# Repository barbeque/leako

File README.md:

A ColecoVision-compatible games console that you can build yourself!

# License
The Leako project is licensed under [the Creative Commons Attribution-NonCommercial 4.0 license](https://creativecommons.org/licenses/by-nc/4.0/).

# Project Introduction
I originally developed this board in order to play some ColecoVision games that I had gotten from the flea market. This turned into several articles on my old-computer repair blog, Leaded Solder:

 - [Part 1](https://www.leadedsolder.com/2020/02/16/colecovision-diy-part-1.html), covering the impetus and design;
 - [Part 2](https://www.leadedsolder.com/2020/07/10/colecovision-diy-part-2.html), covering the assembly and debugging.
 - [Part 3](https://www.leadedsolder.com/2021/10/14/colecovision-diy-part-3.html), covering "digital" joysticks and the Hand Controller
 - [Part 4](https://www.leadedsolder.com/2021/10/26/colecovision-diy-part-4.html), partially covering "quadrature" joysticks such as the steering wheel and Roller Controller

If you enjoyed this project or if you're interested in contributing to future development, I would greatly appreciate a subscription to [the Leaded Solder Patreon](https://www.patreon.com/leadedsolder). The Patreon not only helps me afford to develop expensive projects like this one, but also includes behind-the-scenes posts and previews of upcoming articles.

# Building It Yourself
First, use a PCB fabrication shop such as JLCPCB or PCBWay to order a Gerber file. You can get those from [the Releases page](https://github.com/barbeque/leako/releases).

Stay tuned for a more involved assembly guide, but early adopters are welcome to assemble and test a board.

For the easiest build, you can install [the Interactive BOM Plugin](https://github.com/openscopeproject/InteractiveHtmlBom) and use KiCad to export it. This will give you a click-through visual BOM that makes it really easy to assemble the board. Future versions of this board will come with one of these files in the Release.

You'll want to consult the BOM PDF for the version of the Leako board you wish to assemble. The first truly "working" version was v0.6. I recommend getting [the Gerber ZIPs and BOM from the Releases page](https://github.com/barbeque/leako/releases).

Not all parts on the BOM (Bill of Materials) can be obtained new. Many components are salvaged and can be obtained from eBay or other Chinese-market surplus stores such as AliExpress. Because the sellers and availability are changing constantly, I unfortunately cannot recommend a specific vendor. I suggest ordering from multiple different sellers and building more Leakos with all the leftover parts :)

For a quicker checkout process, [I have constructed a Digi-Key "list"](https://www.digikey.ca/en/mylists/list/FZA1NMR795) which can help you add all of the "new" parts necessary quickly. 

Namely, you will need to find:
 - A TI TMS9918A/TMS9918ANL (_not_ TMS9118, TMS9119, TMS9929, or TMS9928) VDP;
 - A TI SN76489 sound chip;
 - A 27c512-compatible EPROM (a 27c256 may also work but has not been tested);
 - ColecoVision cartridge games;
 - A ColecoVision-compatible controller

Please note the Leako has, so far, only been constructed and tested in NTSC regions. A PAL version would be a very interesting conversion, but would use a chip like a TMS9919 as well as probably some other board changes.

You will also need a USB power supply and a USB-B cable. I recommend using a USB power supply capable of at least 2A - although I have only measured ~450mA max in practice, it would not be a bad idea to have some additional headroom. A lower-quality supply is also likely to introduce more noise. I have tested with two models of Anker PowerPort.

Please also note that at the time of publication, a silicon and fabrication shortage has meant that many parts (for instance, the TI TPS60403 -5V voltage inverter) have become difficult and/or more expensive to locate than when the machine was originally designed. Some have been substituted, but there are likely others.

## Tools
The ColecoVision games and console rely on the presence of a BIOS ROM. In order to program the EPROM with the BIOS, you'll need a copy of the BIOS (it can be dumped from a real ColecoVision) and an EPROM programmer such as a TL866II+.

For soldering surface-mount parts, I strongly recommend a good temperature-controlled soldering iron such as a Hakko FX-888, paste flux, and quality leaded solder from a brand like Kester or MG Chemical. You can use lead-free solder, but I haven't.

# Compatibility
If you have built your own Leako and tested it with a game that's not listed here, please submit a pull request to add it to this list.

| Game          | Works? | Notes |
|---------------|--------|-------|
| Donkey Kong   | Yes    |       |
| Zaxxon        | Yes    |       |
| Time Pilot    | Yes    |       |
| Carnival      | Yes    |       |
| Frenzy        | Yes    |       |
| Ken Uston's Black Jack / Poker | Yes    |       |
| Looping 	| Yes	 |	 |
| Omega Race	| Yes	 | Tested with Hand Controller |

| Peripheral    | Works? | Notes |
|---------------|--------|-------|
| ColecoVision controller | Yes | |
| ADAM controller | Yes | |
| Super Action Controller | Yes | Tested with _Super Action Baseball_ only |
| Roller Controller | Partial | Tested with _Slither_ only; my controller is not working properly, even on a real ColecoVision |
| Expansion Module #2 (steering controller) | Partial | Tested with _Turbo_ only; my controller is not working properly, even on a real ColecoVision |

The latter two will be re-investigated as the controllers are tested, and hopefully this table will be updated with some better news in the future.

Please note:
 * The Leako board does not have a ColecoVision expansion connector, so it cannot work with any Expansion Modules, including the ADAM.
 * The Leako board does not have a ColecoVision power connector, so the Roller Controller will need to be powered independently using a ColecoVision power supply such as the ColUSB, or wired for a +5V source such as a USB cable.

# Known Issues
## "Always On" phenomenon
If you power the Leako off a monitor or television set that is also being used to display the Leako, it can complete the "ground" circuit from the USB jack through the composite video jack and keep the Leako turned on, bypassing the power switch entirely. In this scenario, the Leako will remain powered on, regardless of the power switch position.

To work around this problem, try powering the Leako from a different USB power source, or use a television that isolates USB ground from video ground.

Thank you to Cheshire Noir and Tom Storey for figuring this one out.

# Version History
## v0.8
More small fixes.
 * Move U20/U11 to other side of board so cartridges with extra long skirts or loose PCBs won't interfere with them.
 * Move mounting hole added in previous step to side of cartridge slot, so you don't have to use a low-profile screw head there anymore.
 * Larger pads on the 74LS574s, to ease soldering.
 * It is now much harder to hit the video filtering capacitor with the tip of a video cable.
 * Upgraded project files to KiCad 6

## v0.7
Many small fixes, mostly around reliability.
 * Correct missing junction from D3/D4 to R35 (EXT_QUAD pulldown.) Thank you to Oliver Fiero for catching this.
 * Unused logic inputs grounded to reduce power consumption.
 * Change controller ports from generic KiCad DE9 footprint to AE10968-ND
 * Change -5V charge pump because of parts shortage. Now ICL7660.
 * Controller port numbers on schematic now reflect actual logical controller ports.
 * Barrel jack 5V replaced with USB-B to broaden availability of high-quality regulated power supplies.
 * Additional mounting hole behind cartridge to reduce amount of board flex when cartridges are inserted and removed.
 * Thicker power traces.
 * Passives now labeled on board where possible, to speed assembly.

## v0.6
First working version.

# Links
 - [Console5 schematics and parts list](https://console5.com/wiki/Colecovision)
 - ChildOfCv's [better schematics](https://atariage.com/forums/topic/285656-new-colecovision-schematics/)
 - [Datasheet for LC331632M-12 SRAM](https://www.datasheet4u.com/datasheet-pdf/Sanyo/LC331632M-12/pdf.php?id=391797)
 - [Leonardo Miliani's SRAM video mod](https://www.leonardomiliani.com/en/2019/lm80c-tms9918a/)

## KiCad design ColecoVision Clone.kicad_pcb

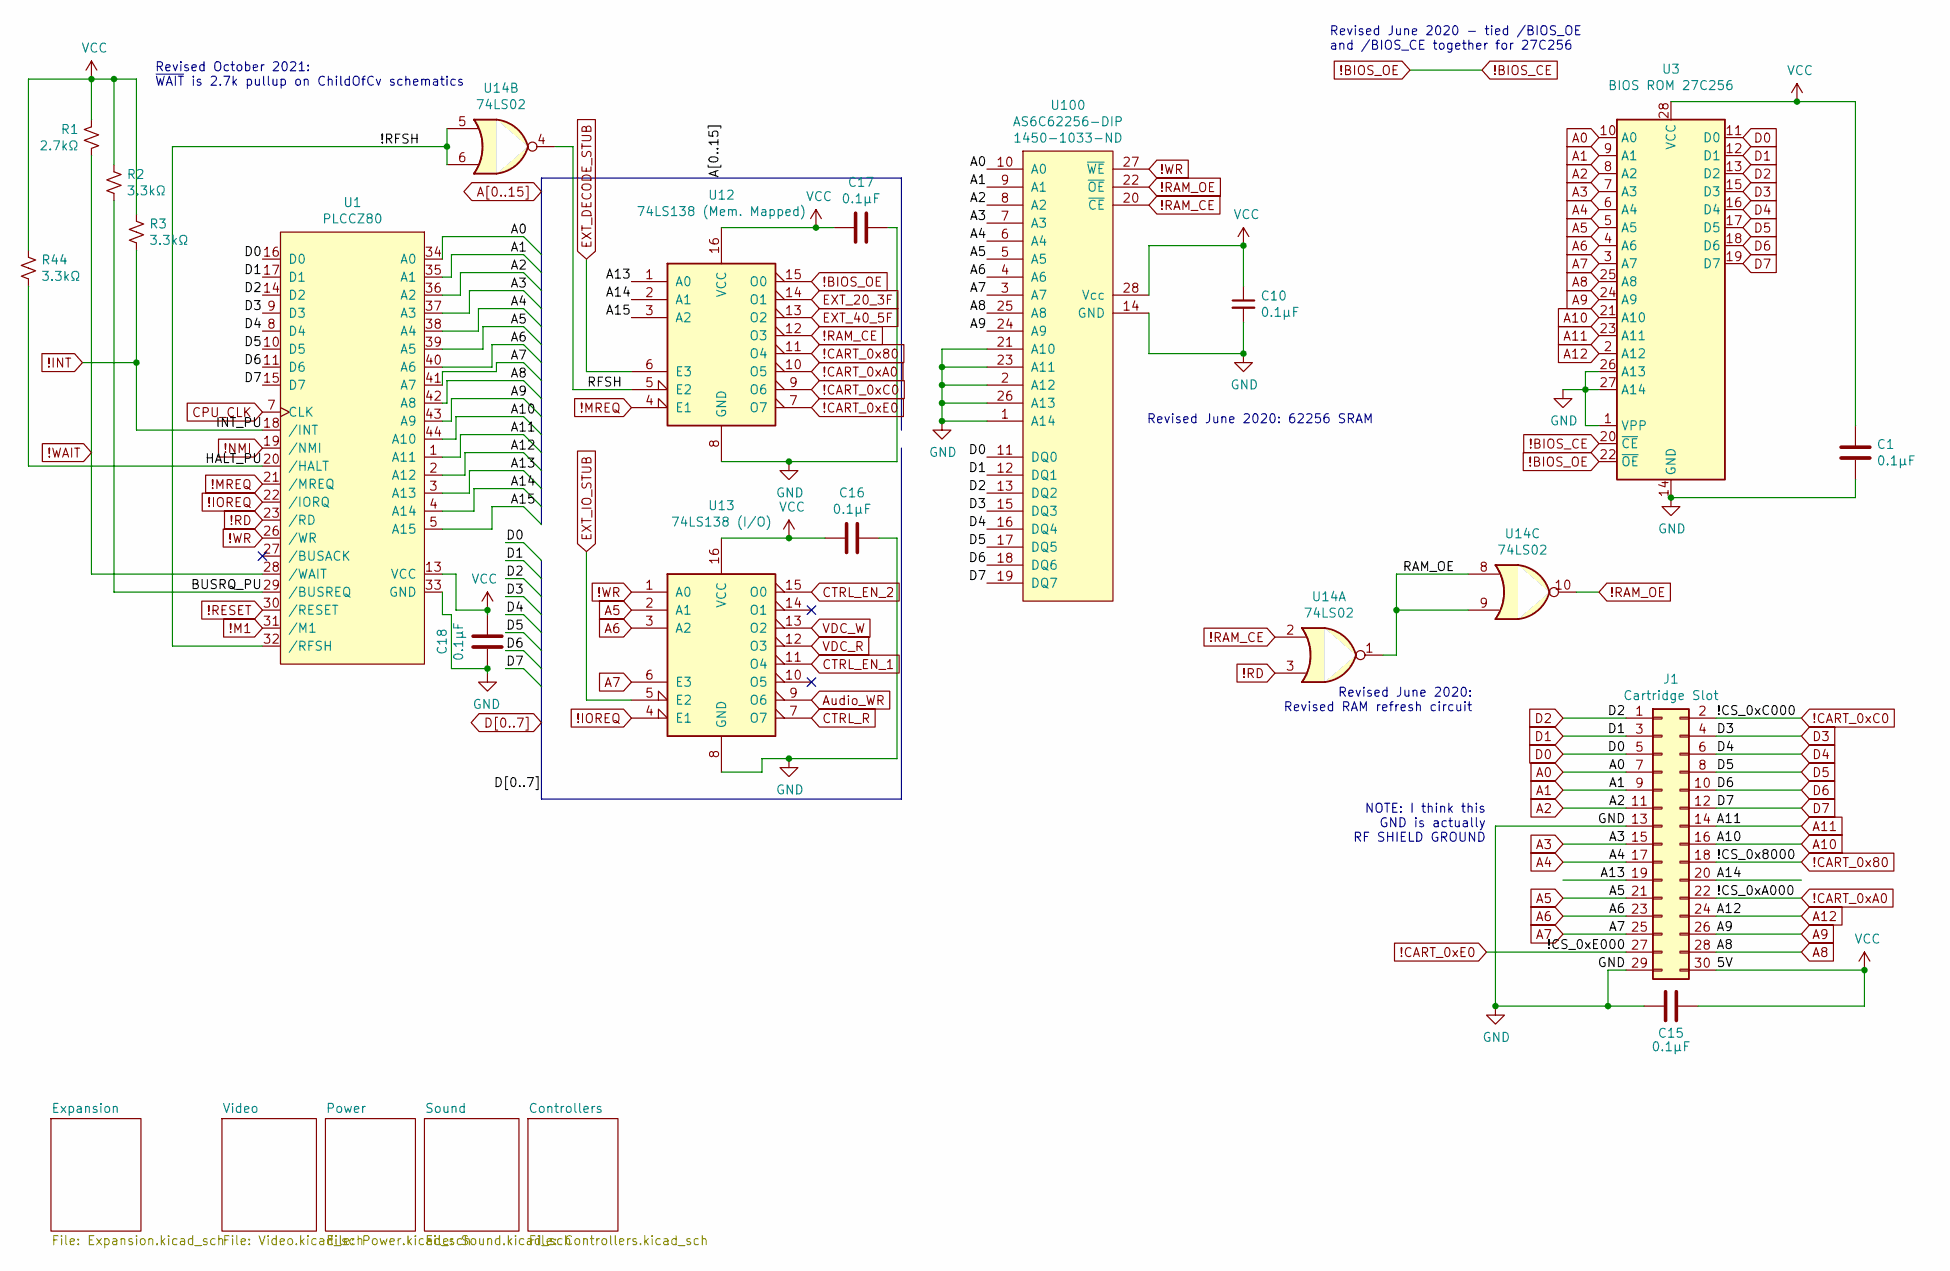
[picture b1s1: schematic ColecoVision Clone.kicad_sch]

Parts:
C1, C10, C15, C16, C17, C18: 0.1µF; C_0805_HandSoldering; DigiKey 1276-1099-1-ND
J1: Cartridge Slot; Sullins_Cart_Slot; DigiKey A31715-ND
R1: 2.7kΩ; R_0805_HandSoldering; DigiKey RMCF0805JT2K70CT-ND
R2, R3, R44: 3.3kΩ; R_0805_HandSoldering; DigiKey RMCF0805JT3K30CT-ND
U1: PLCCZ80; PLCC44; DigiKey 2057-PLCC-44-AT-ND; 269-3899-ND
U3: BIOS ROM 27C256; DIP-28_W15.24mm_Socket_LongPads; DigiKey 2057-ICS-628-T-ND
U12: 74LS138 (Mem. Mapped); SOIC-16_3.9x9.9mm_Pitch1.27mm; DigiKey 296-14883-2-ND
U13: 74LS138 (I/O); SOIC-16_3.9x9.9mm_Pitch1.27mm; DigiKey 296-14883-2-ND
U14: 74LS02; SOIC-14_3.9x8.7mm_Pitch1.27mm; DigiKey 296-14874-1-ND
U100: AS6C62256-DIP; DIP-28_W15.24mm_Socket_LongPads; DigiKey 1450-1033-ND

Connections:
!BIOS_CE: U3.20 (~CE), U3.22 (~OE), U12.15 (O0)
!CART_0x80: J1.18, U12.11 (O4)
!CART_0xA0: J1.22, U12.10 (O5)
!CART_0xC0: J1.2, U12.9 (O6)
!CART_0xE0: J1.27, U12.7 (O7)
!INT: R3.2, U1.18 (/INT); also elsewhere on the board
!IOREQ: U1.22 (/IORQ), U13.4 (E1)
!M1: U1.31 (/M1); also elsewhere on the board
!MREQ: U1.21 (/MREQ), U12.4 (E1)
!NMI: U1.19 (/NMI); also elsewhere on the board
!RAM_CE: U12.12 (O3), U14.2, U100.20 (~CE)
!RAM_OE: U14.10, U100.22 (~OE)
!RD: U1.23 (/RD), U14.3
!RESET: U1.30 (/RESET); also elsewhere on the board
!WAIT: R1.2, U1.28 (/WAIT); also elsewhere on the board
!WR: U1.26 (/WR), U13.1 (A0), U100.27 (~WE)
/!RFSH: U1.32 (/RFSH), U14.5, U14.6
/BUSRQ_PU: R2.2, U1.29 (/BUSREQ)
/HALT_PU: R44.2, U1.20 (/HALT)
/RAM_OE: U14.1, U14.8, U14.9
/RFSH: U12.5 (E2), U14.4
A0: J1.7, U1.34 (A0), U3.10 (A0), U100.10 (A0); also elsewhere on the board
A1: J1.9, U1.35 (A1), U3.9 (A1), U100.9 (A1); also elsewhere on the board
A2: J1.11, U1.36 (A2), U3.8 (A2), U100.8 (A2)
A3: J1.15, U1.37 (A3), U3.7 (A3), U100.7 (A3)
A4: J1.17, U1.38 (A4), U3.6 (A4), U100.6 (A4)
A5: J1.21, U1.39 (A5), U3.5 (A5), U13.2 (A1), U100.5 (A5)
A6: J1.23, U1.40 (A6), U3.4 (A6), U13.3 (A2), U100.4 (A6)
A7: J1.25, U1.41 (A7), U3.3 (A7), U13.6 (E3), U100.3 (A7)
A8: J1.28, U1.42 (A8), U3.25 (A8), U100.25 (A8)
A9: J1.26, U1.43 (A9), U3.24 (A9), U100.24 (A9)
A10: J1.16, U1.44 (A10), U3.21 (A10)
A11: J1.14, U1.1 (A11), U3.23 (A11)
A12: J1.24, U1.2 (A12), U3.2 (A12)
A13: J1.19, U1.3 (A13), U12.1 (A0)
A14: J1.20, U1.4 (A14), U12.2 (A1)
A15: U1.5 (A15), U12.3 (A2)
Audio_WR: U13.9 (O6); also elsewhere on the board
CPU_CLK: U1.7 (CLK); also elsewhere on the board
CTRL_EN_1: U13.11 (O4); also elsewhere on the board
CTRL_EN_2: U13.15 (O0); also elsewhere on the board
CTRL_R: U13.7 (O7); also elsewhere on the board
D0: J1.5, U1.16 (D0), U3.11 (D0), U100.11 (DQ0); also elsewhere on the board
D1: J1.3, U1.17 (D1), U3.12 (D1), U100.12 (DQ1); also elsewhere on the board
D2: J1.1, U1.14 (D2), U3.13 (D2), U100.13 (DQ2); also elsewhere on the board
D3: J1.4, U1.9 (D3), U3.15 (D3), U100.15 (DQ3); also elsewhere on the board
D4: J1.6, U1.8 (D4), U3.16 (D4), U100.16 (DQ4); also elsewhere on the board
D5: J1.8, U1.10 (D5), U3.17 (D5), U100.17 (DQ5); also elsewhere on the board
D6: J1.10, U1.11 (D6), U3.18 (D6), U100.18 (DQ6); also elsewhere on the board
D7: J1.12, U1.15 (D7), U3.19 (D7), U100.19 (DQ7); also elsewhere on the board
EXT_20_3F: U12.14 (O1)
EXT_40_5F: U12.13 (O2)
EXT_DECODE_STUB: U12.6 (E3); also elsewhere on the board
EXT_IO_STUB: U13.5 (E2); also elsewhere on the board
GND: C1.2, C10.2, C15.2, C16.1, C17.2, C18.1, J1.13, J1.29, U1.33 (GND), U3.1 (VPP), U3.14 (GND), U3.26 (A13), U3.27 (A14), U12.8 (GND), U13.8 (GND), U100.1 (A14), U100.2 (A12), U100.14 (GND), U100.21 (A10), U100.23 (A11), U100.26 (A13); also elsewhere on the board
VCC: C1.1, C10.1, C15.1, C16.2, C17.1, C18.2, J1.30, R1.1, R2.1, R3.1, R44.1, U1.13 (VCC), U3.28 (VCC), U12.16 (VCC), U13.16 (VCC), U100.28 (Vcc); also elsewhere on the board
VDC_R: U13.12 (O3); also elsewhere on the board
VDC_W: U13.13 (O2); also elsewhere on the board

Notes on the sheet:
Revised June 2020: Revised RAM refresh circuit
Revised June 2020: 62256 SRAM
Revised June 2020 - tied /BIOS_OE and /BIOS_CE together for 27C256
Revised October 2021: ~{WAIT} is 2.7k pullup on ChildOfCv schematics
NOTE: I think this GND is actually RF SHIELD GROUND

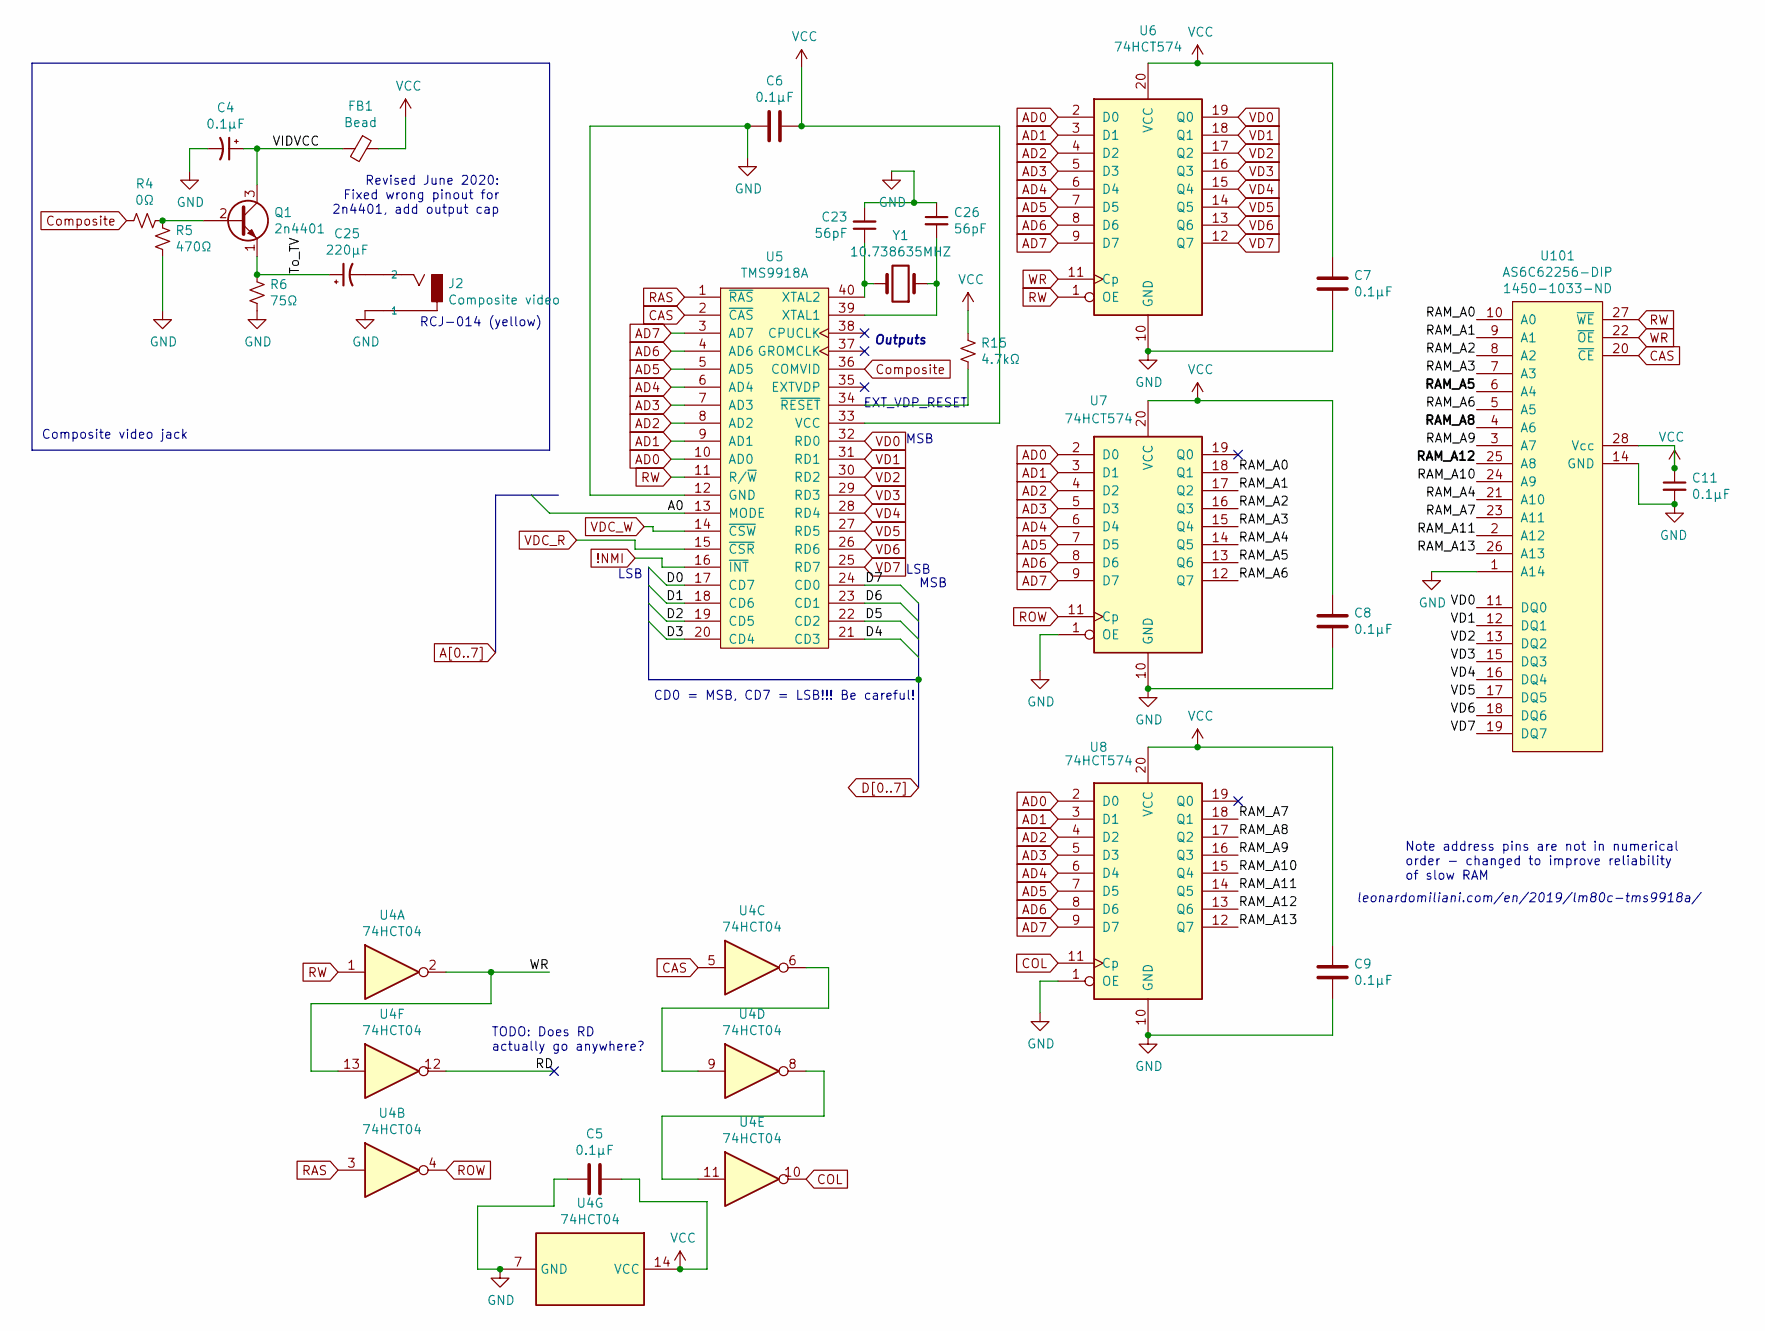
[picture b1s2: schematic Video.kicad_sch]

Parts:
C4, C5, C6, C7, C8, C9, C11: 0.1µF; C_0805_HandSoldering; DigiKey 1276-1099-1-ND
C23, C26: 56pF; C_0805_HandSoldering; DigiKey 732-7817-1-ND
C25: 220µF; CP_Radial_D6.3mm_P2.50mm; DigiKey 493-15121-ND
FB1: Bead; Choke_SMD_1206_Handsoldering; DigiKey 283-MFBW1V3216-310-RCT-ND
J2: Composite video; CUI_RCJ-017; DigiKey CP-1403-ND‎
Q1: 2n4401; TO-92_Inline_Wide; DigiKey 2N4401TFCT-ND
R4: 0Ω; R_0805_HandSoldering; DigiKey RMCF0805ZT0R00CT-ND
R5: 470Ω; R_0805_HandSoldering; DigiKey RMCF0805JT470RCT-ND
R6: 75Ω; R_0805_HandSoldering; DigiKey RMCF0805JT75R0CT-ND
R15: 4.7kΩ; R_0805_HandSoldering; DigiKey RMCF0805JT4K70CT-ND
U4: 74HCT04; SOIC-14_3.9x8.7mm_Pitch1.27mm; DigiKey 296-31832-1-ND
U5: TMS9918A; DIP-40_W15.24mm_Socket_LongPads; DigiKey ED3048-5-ND
U6, U7, U8: 74HCT574; SOIC-20W_7.5x12.8mm_P1.27mm_LongLegs; DigiKey 1727-2856-1-ND
U101: AS6C62256-DIP; DIP-28_W15.24mm_Socket_LongPads; DigiKey 1450-1033-ND
Y1: 10.738635MHZ; Crystal_HC49-U_Vertical; DigiKey CTX1443-ND

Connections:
!NMI: U5.16 (~INT); also elsewhere on the board
/Video/RAM_A0: U7.18 (Q1), U101.10 (A0)
/Video/RAM_A1: U7.17 (Q2), U101.9 (A1)
/Video/RAM_A2: U7.16 (Q3), U101.8 (A2)
/Video/RAM_A3: U7.15 (Q4), U101.7 (A3)
/Video/RAM_A4: U7.14 (Q5), U101.21 (A10)
/Video/RAM_A5: U7.13 (Q6), U101.6 (A4)
/Video/RAM_A6: U7.12 (Q7), U101.5 (A5)
/Video/RAM_A7: U8.18 (Q1), U101.23 (A11)
/Video/RAM_A8: U8.17 (Q2), U101.4 (A6)
/Video/RAM_A9: U8.16 (Q3), U101.3 (A7)
/Video/RAM_A10: U8.15 (Q4), U101.24 (A9)
/Video/RAM_A11: U8.14 (Q5), U101.2 (A12)
/Video/RAM_A12: U8.13 (Q6), U101.25 (A8)
/Video/RAM_A13: U8.12 (Q7), U101.26 (A13)
/Video/RD: U4.12
/Video/To_TV: C25.1, Q1.1 (E), R6.1
/Video/VIDVCC: C4.1, FB1.2, Q1.3 (C)
A0: U5.13 (MODE); also elsewhere on the board
AD0: U5.10 (AD0), U6.2 (D0), U7.2 (D0), U8.2 (D0)
AD1: U5.9 (AD1), U6.3 (D1), U7.3 (D1), U8.3 (D1)
AD2: U5.8 (AD2), U6.4 (D2), U7.4 (D2), U8.4 (D2)
AD3: U5.7 (AD3), U6.5 (D3), U7.5 (D3), U8.5 (D3)
AD4: U5.6 (AD4), U6.6 (D4), U7.6 (D4), U8.6 (D4)
AD5: U5.5 (AD5), U6.7 (D5), U7.7 (D5), U8.7 (D5)
AD6: U5.4 (AD6), U6.8 (D6), U7.8 (D6), U8.8 (D6)
AD7: U5.3 (AD7), U6.9 (D7), U7.9 (D7), U8.9 (D7)
CAS: U4.5, U5.2 (~CAS), U101.20 (~CE)
COL: U4.10, U8.11 (Cp)
Composite: R4.2, U5.36 (COMVID)
D0: U5.17 (CD7); also elsewhere on the board
D1: U5.18 (CD6); also elsewhere on the board
D2: U5.19 (CD5); also elsewhere on the board
D3: U5.20 (CD4); also elsewhere on the board
D4: U5.21 (CD3); also elsewhere on the board
D5: U5.22 (CD2); also elsewhere on the board
D6: U5.23 (CD1); also elsewhere on the board
D7: U5.24 (CD0); also elsewhere on the board
GND: C4.2, C5.2, C6.2, C7.2, C8.2, C9.2, C11.2, C23.2, C26.1, J2.1A (1), J2.1B (1), J2.1C (1), R5.2, R6.2, U4.7 (GND), U5.12 (GND), U6.10 (GND), U7.1 (OE), U7.10 (GND), U8.1 (OE), U8.10 (GND), U101.1 (A14), U101.14 (GND); also elsewhere on the board
unnamed: C23.1, U5.40 (XTAL2), Y1.2
unnamed: C25.2, J2.2
unnamed: C26.2, U5.39 (XTAL1), Y1.1
unnamed: Q1.2 (B), R4.1, R5.1
unnamed: R15.2, U5.34 (~RESET)
unnamed: U4.6, U4.9
unnamed: U4.8, U4.11
RAS: U4.3, U5.1 (~RAS)
ROW: U4.4, U7.11 (Cp)
RW: U4.1, U5.11 (R/~W), U6.1 (OE), U101.27 (~WE)
VCC: C5.1, C6.1, C7.1, C8.1, C9.1, C11.1, FB1.1, R15.1, U4.14 (VCC), U5.33 (VCC), U6.20 (VCC), U7.20 (VCC), U8.20 (VCC), U101.28 (Vcc); also elsewhere on the board
VD0: U5.32 (RD0), U6.19 (Q0), U101.11 (DQ0)
VD1: U5.31 (RD1), U6.18 (Q1), U101.12 (DQ1)
VD2: U5.30 (RD2), U6.17 (Q2), U101.13 (DQ2)
VD3: U5.29 (RD3), U6.16 (Q3), U101.15 (DQ3)
VD4: U5.28 (RD4), U6.15 (Q4), U101.16 (DQ4)
VD5: U5.27 (RD5), U6.14 (Q5), U101.17 (DQ5)
VD6: U5.26 (RD6), U6.13 (Q6), U101.18 (DQ6)
VD7: U5.25 (RD7), U6.12 (Q7), U101.19 (DQ7)
VDC_R: U5.15 (~CSR); also elsewhere on the board
VDC_W: U5.14 (~CSW); also elsewhere on the board
WR: U4.2, U4.13, U6.11 (Cp), U101.22 (~OE)

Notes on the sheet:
leonardomiliani.com/en/2019/lm80c-tms9918a/
TODO: Does RD actually go anywhere?
EXT_VDP_RESET
LSB
CD0 = MSB, CD7 = LSB!!! Be careful!
Composite video jack
Note address pins are not in numerical order - changed to improve reliability of slow RAM
RCJ-014 (yellow)
Revised June 2020: Fixed wrong pinout for 2n4401, add output cap
MSB
Outputs

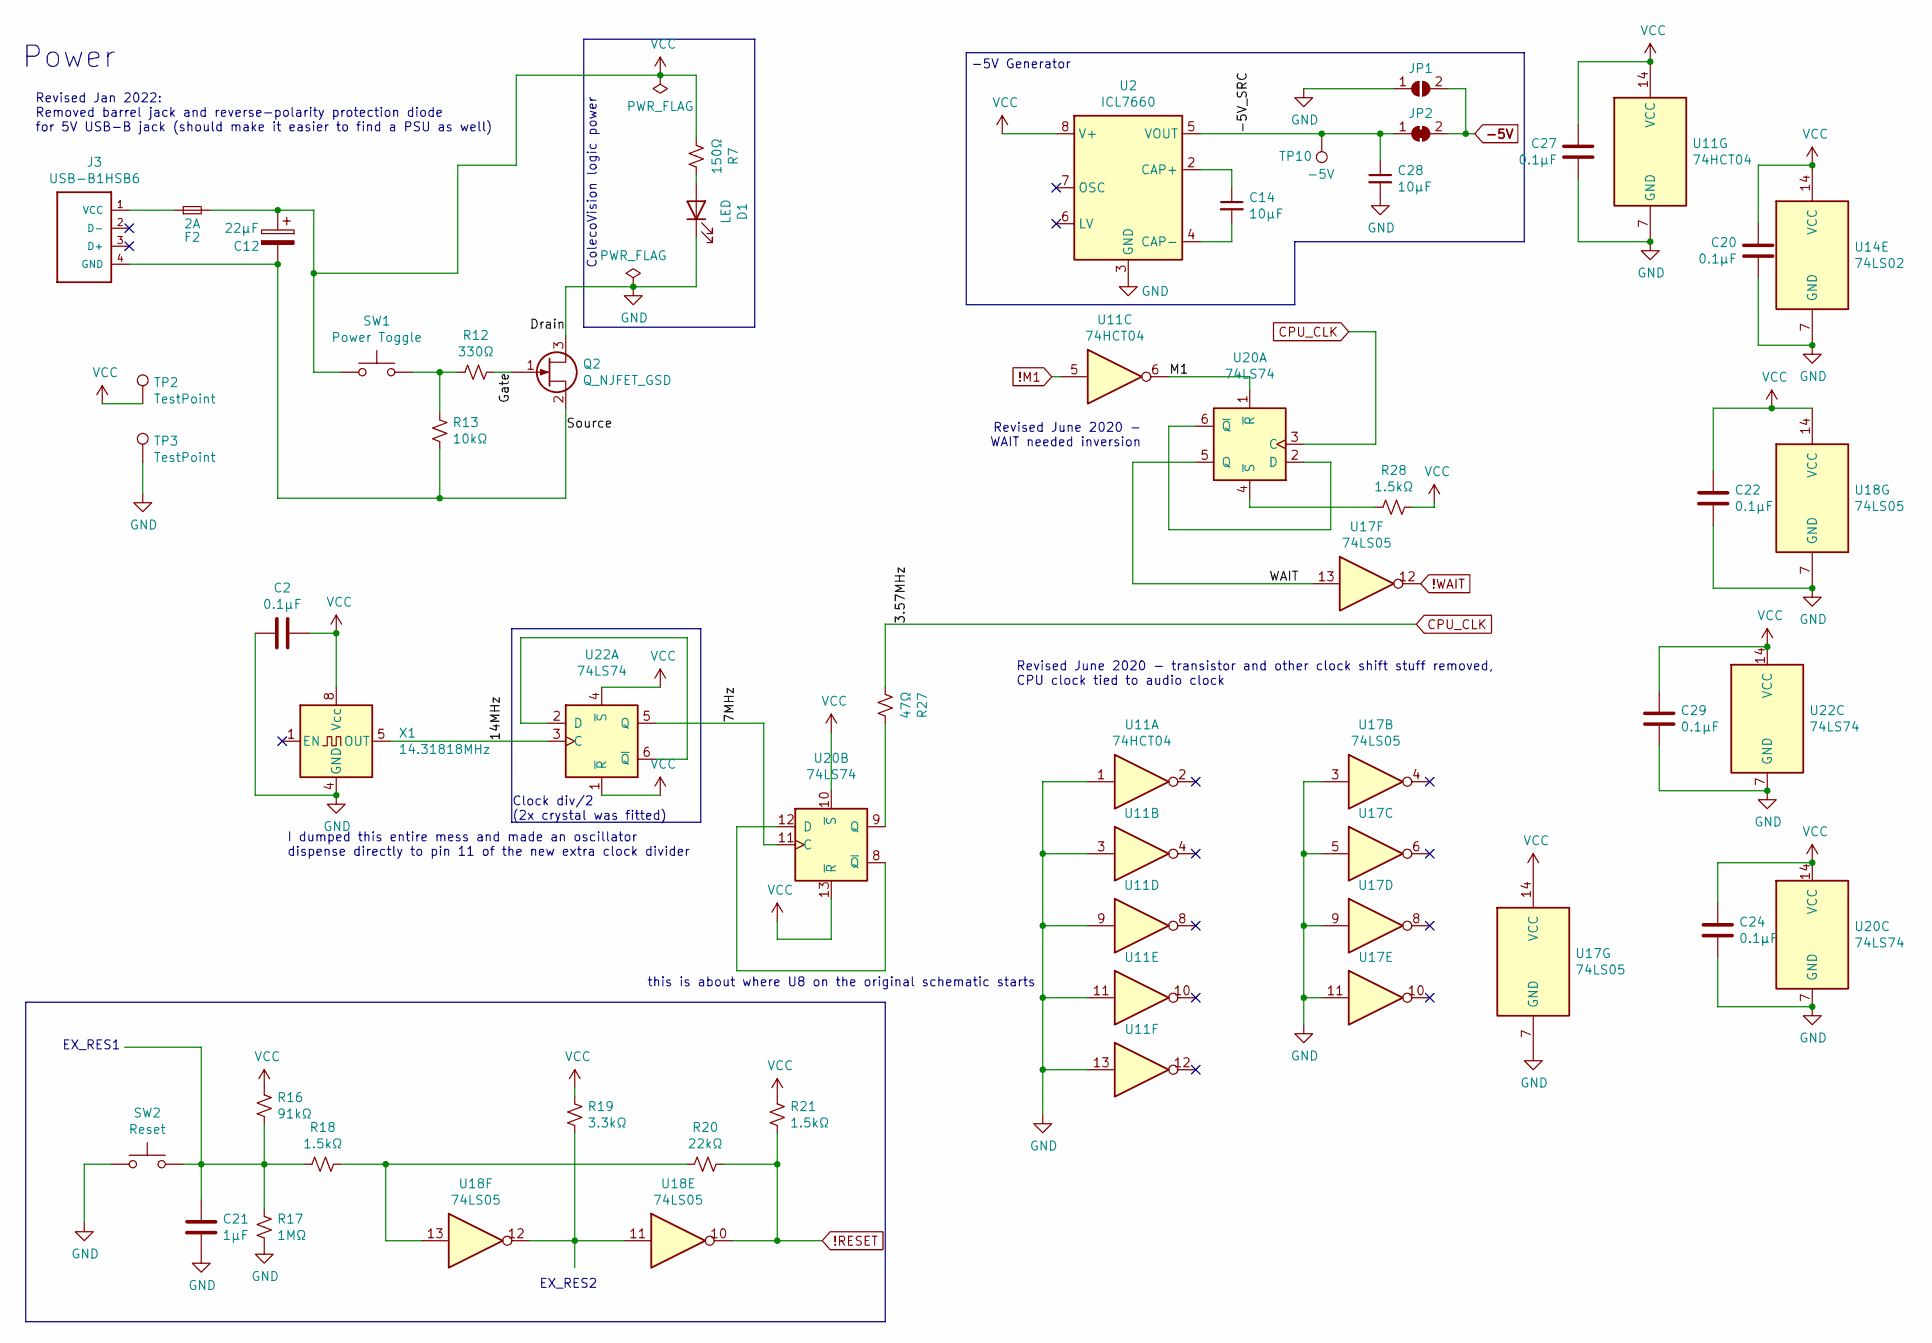
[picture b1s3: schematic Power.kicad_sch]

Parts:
C2, C20, C22, C24, C27, C29: 0.1µF; C_0805_HandSoldering; DigiKey 1276-1099-1-ND
C12: 22µF; CP_Radial_D5.0mm_P2.50mm; DigiKey 493-1037-ND
C14, C28: 10µF; C_0805_2012Metric_Pad1.15x1.40mm_HandSolder; DigiKey 1276-1298-1-ND
C21: 1µF; C_0805_HandSoldering; DigiKey 1276-2926-1-ND
D1: LED; LED_D3.0mm; DigiKey 1497-1022-ND
F2: 2A; 0251002.MRT1L; DigiKey F3171CT-ND
J3: USB-B1HSB6; OST_USB-B1HSB6; DigiKey ED2982-ND
JP1: SolderJumper_2_Open; SolderJumper-2_P1.3mm_Open_Pad1.0x1.5mm
JP2: SolderJumper_2_Bridged; SolderJumper-2_P1.3mm_Bridged_Pad1.0x1.5mm
Q2: Q_NJFET_GSD; SOT-23_Handsoldering; DigiKey DMN2046U-7DICT-ND
R7: 150Ω; R_0805_HandSoldering; DigiKey RMCF0805JT150RCT-ND
R12: 330Ω; R_0805_HandSoldering; DigiKey RMCF0805JT330RCT-ND
R13: 10kΩ; R_0805_HandSoldering; DigiKey RMCF0805JT10K0CT-ND
R16: 91kΩ; R_0805_HandSoldering; DigiKey RMCF0805JT91K0CT-ND
R17: 1MΩ; R_0805_HandSoldering; DigiKey RMCF0805JT1M00CT-ND
R18, R21, R28: 1.5kΩ; R_0805_HandSoldering; DigiKey RMCF0805FT1K00CT-ND
R19: 3.3kΩ; R_0805_HandSoldering; DigiKey RMCF0805JT3K30CT-ND
R20: 22kΩ; R_0805_HandSoldering; DigiKey RMCF0805JT22K0CT-ND
R27: 47Ω; R_0805_HandSoldering; DigiKey RMCF0805JT47R0CT-ND
SW1: Power Toggle; PVA1_Switch; DigiKey 401-1132-ND
SW2: Reset; SW_PUSH_6mm; DigiKey 679-2428-ND
TP2, TP3: TestPoint; Measurement_Point_Round-TH_Small
TP10: -5V; TestPoint_Loop_D1.80mm_Drill1.0mm_Beaded
U2: ICL7660; SOIC-8_3.9x4.9mm_P1.27mm; DigiKey ICL7660CSA+TCT-ND
U11: 74HCT04; SOIC-14_3.9x8.7mm_Pitch1.27mm; DigiKey 296-31832-1-ND
U14: 74LS02; SOIC-14_3.9x8.7mm_Pitch1.27mm; DigiKey 296-14874-1-ND
U17: 74LS05; DigiKey 296-1630-1-ND
U18: 74LS05; SOIC-14_3.9x8.7mm_Pitch1.27mm; DigiKey 296-1630-1-ND
U20, U22: 74LS74; SOIC-14_3.9x8.7mm_Pitch1.27mm; DigiKey 296-14899-1-ND
X1: 14.31818MHz; Oscillator_DIP-8_LargePads; DigiKey 535-9170-5-ND

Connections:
!M1: U11.5; also elsewhere on the board
!RESET: R20.1, R21.2, U18.10; also elsewhere on the board
!WAIT: U17.12; also elsewhere on the board
-5V: JP1.2 (B), JP2.2 (B); also elsewhere on the board
/Power/7MHz: U20.11 (C), U22.5 (Q)
/Power/14MHz: U22.3 (C), X1.5 (OUT)
/Power/-5V_SRC: C28.1, JP2.1 (A), TP10.1, U2.5 (VOUT)
/Power/Gate: Q2.1 (G), R12.1
/Power/M1: U11.6, U20.1 (~R)
/Power/Source: C12.2, J3.4 (GND), Q2.2 (S), R13.2
/Power/WAIT: U17.13, U20.5 (Q)
CPU_CLK: R27.2, U20.3 (C); also elsewhere on the board
GND: C2.2, C20.1, C21.2, C22.2, C24.2, C27.1, C28.2, C29.2, D1.1 (K), JP1.1 (A), Q2.3 (D), R17.2, SW2.1, TP3.1, U2.3 (GND), U11.1, U11.3, U11.7 (GND), U11.9, U11.11, U11.13, U14.7 (GND), U17.3, U17.5, U17.7 (GND), U17.9, U17.11, U18.7 (GND), U20.7 (GND), U22.7 (GND), X1.4 (GND); also elsewhere on the board
unnamed: C14.1, U2.2 (CAP+)
unnamed: C14.2, U2.4 (CAP-)
unnamed: C21.1, R16.2, R17.1, R18.2, SW2.2
unnamed: D1.2 (A), R7.1
unnamed: F2.1, J3.1 (VCC)
unnamed: R12.2, R13.1, SW1.2
unnamed: R18.1, R20.2, U18.13
unnamed: R19.2, U18.11, U18.12
unnamed: R27.1, U20.9 (Q)
unnamed: R28.2, U20.4 (~S)
unnamed: U20.2 (D), U20.6 (~Q)
unnamed: U20.8 (~Q), U20.12 (D)
unnamed: U22.2 (D), U22.6 (~Q)
VCC: C2.1, C12.1, C20.2, C22.1, C24.1, C27.2, C29.1, F2.2, R7.2, R16.1, R19.1, R21.1, R28.1, SW1.1, TP2.1, U2.8 (V+), U11.14 (VCC), U14.14 (VCC), U17.14 (VCC), U18.14 (VCC), U20.10 (~S), U20.13 (~R), U20.14 (VCC), U22.1 (~R), U22.4 (~S), U22.14 (VCC), X1.8 (Vcc); also elsewhere on the board

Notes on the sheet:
Power
Revised June 2020 - WAIT needed inversion
ColecoVision logic power
I dumped this entire mess and made an oscillator dispense directly to pin 11 of the new extra clock divider
EX_RES2
Revised June 2020 - transistor and other clock shift stuff removed, CPU clock tied to audio clock
Clock div/2 (2x crystal was fitted)
Revised Jan 2022: Removed barrel jack and reverse-polarity protection diode for 5V USB-B jack (should make it easier to find a PSU as well)
EX_RES1
this is about where U8 on the original schematic starts
-5V Generator

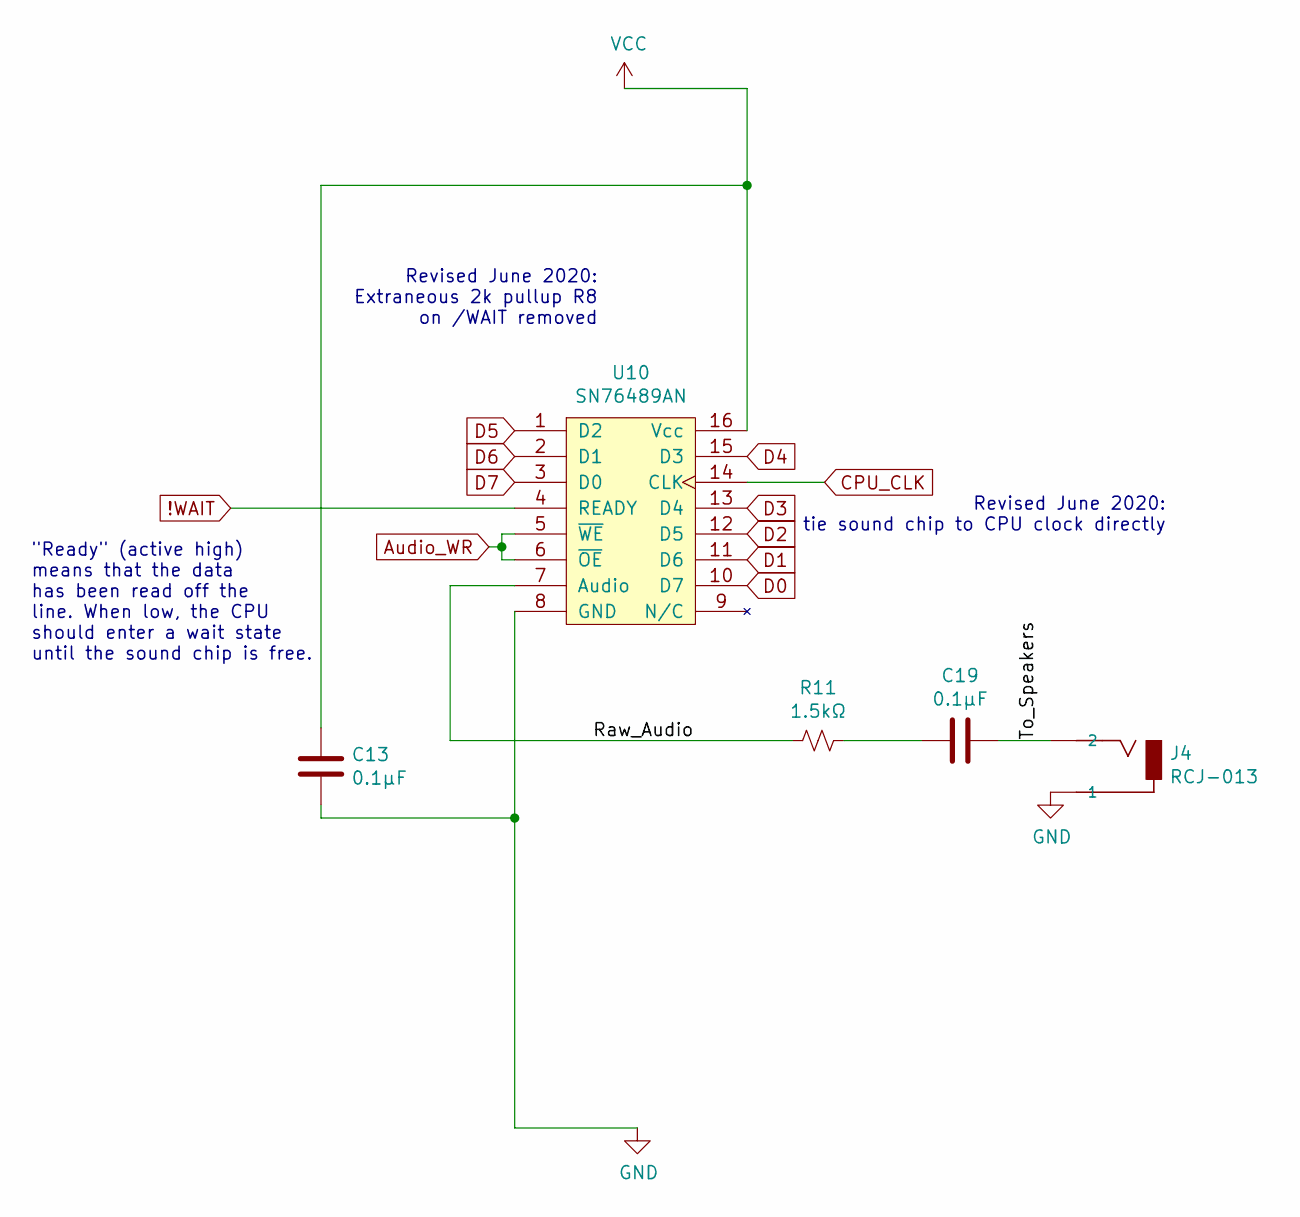
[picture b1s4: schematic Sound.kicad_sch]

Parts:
C13, C19: 0.1µF; C_0805_HandSoldering; DigiKey 1276-1099-1-ND
J4: RCJ-013; CUI_RCJ-017; DigiKey CP-1402-ND‎
R11: 1.5kΩ; R_0805_HandSoldering; DigiKey RMCF0805FT1K00CT-ND
U10: SN76489AN; DIP-16_W7.62mm_Socket_LongPads; DigiKey AE9992-ND

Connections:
!WAIT: U10.4 (READY); also elsewhere on the board
/Sound/Raw_Audio: R11.2, U10.7 (Audio)
/Sound/To_Speakers: C19.1, J4.2
Audio_WR: U10.5 (~WE), U10.6 (~OE); also elsewhere on the board
CPU_CLK: U10.14 (CLK); also elsewhere on the board
D0: U10.10 (D7); also elsewhere on the board
D1: U10.11 (D6); also elsewhere on the board
D2: U10.12 (D5); also elsewhere on the board
D3: U10.13 (D4); also elsewhere on the board
D4: U10.15 (D3); also elsewhere on the board
D5: U10.1 (D2); also elsewhere on the board
D6: U10.2 (D1); also elsewhere on the board
D7: U10.3 (D0); also elsewhere on the board
GND: C13.2, J4.1A (1), J4.1B (1), J4.1C (1), U10.8 (GND); also elsewhere on the board
unnamed: C19.2, R11.1
VCC: C13.1, U10.16 (Vcc); also elsewhere on the board

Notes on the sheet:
"Ready" (active high) means that the data has been read off the line. When low, the CPU should enter a wait state until the sound chip is free.
Revised June 2020: Extraneous 2k pullup R8 on /WAIT removed
Revised June 2020: tie sound chip to CPU clock directly

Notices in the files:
parts and their libraries:
Copyright 2016 Accelerated Designs. All rights reserved.
Copyright 2021 Accelerated Designs. All rights reserved.
